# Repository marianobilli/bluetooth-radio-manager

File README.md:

# Bluetooth Radio Manager

A self-contained, battery-powered box that puts **four 2.4 GHz radios** under one **ESP32-S3**, with a small OLED and encoder UI, in a 3D-printed case. Each radio slot takes an nRF24L01+PA+LNA or an Ebyte E01-2G4M27D, and the firmware decides what the four radios do: range tests, multi-channel sniffing, relays, mesh experiments, or anything else that needs several 2.4 GHz radios in one hand-held unit.

Everything is open: the KiCad board, the parametric case, the fab files and the firmware skeleton are in this repository.

## Contents

1. [Overview](#1-overview)
2. [PCB and components](#2-pcb-and-components)
3. [Ordering the PCB](#3-ordering-the-pcb)
4. [Ordering the case](#4-ordering-the-case)
5. [Firmware skeleton](#5-firmware-skeleton)

---

## 1. Overview

| | |
|---|---|
| **Radios** | 4 slots, 2×4 socket each, nRF24L01+PA+LNA or E01-2G4M27D, SMA antennas out the back |
| **Controller** | YD-ESP32-23 (ESP32-S3 DevKitC-1 clone, 16 MB flash, 8 MB PSRAM), socketed |
| **UI** | 1.3" I²C OLED, EC11 encoder with push, BACK and CONFIRM buttons, on a plug-in module |
| **Power** | Two 5 V USB-C sockets in the case: one supply of 2 A or more, or two smaller power banks. 3.5 to 10 h of continuous transmit |
| **Board** | 96.5 × 73.2 mm, 2 layers, all through-hole and socketed, hand-solderable |
| **Case** | Two-part 3D print, snap latches, vented, 103 × 103 × 26 mm, 41 mm to the top of the knob, antennas extra. One case fits either radio |
| **Firmware** | PlatformIO, Arduino framework, native and on-device tests |

The carrier board does only three things: power the radios correctly, wire them to one SPI bus with separate select and interrupt lines, and hold the modules so they can be swapped without tools. Everything else is firmware.

---

## 2. PCB and components

### Bill of materials

| Ref | Part | Role |
|-----|------|------|
| M1–M4 | 2×4 female header, 2.54 mm | Radio slots, along the top edge so the modules and antennas hang off the board |
| U1 | YD-ESP32-23 on 2 × 1×22 female headers | Controller, drives all four radios over one SPI bus |
| J1 | UI module on 1×9 female header + 4 × M3 standoffs | OLED, encoder, BACK and CONFIRM buttons |
| U2 | LD1117V33, TO-220, mounted flat | Shared 3.3 V rail for nRF24 slots, 800 mA |
| D1 | 1N5819 Schottky, DO-41 | Feeds the devkit from input A and stops its USB power reaching the radios |
| D2, D3 | SB240 Schottky (40 V, 2 A), DO-15 | Cross-feed between inputs A and B, so one supply can power the whole board |
| JP1–JP4 | 1×3 pin header + shunt | Radio slot supply select, 5 V or 3.3 V |
| C3–C6 | 220 µF / 10 V electrolytic | Bulk capacitor per radio slot, for TX bursts |
| C7–C10 | 100 nF ceramic | Decoupling per radio slot |
| C1, C2 | 470 µF / 10 V electrolytic | Bulk capacitor on each 5 V input |
| C11, C12 | 10 µF / 16 V electrolytic | LD1117 input and output |
| J2, J3 | JST-XH 2-pin | 5 V inputs A and B, pigtails from the case's USB-C sockets |
| MH1–MH4 | M3 holes | Case mounting |

### Radio modules and jumpers

Both modules share the nRF24L01 2×4 pinout (GND, VCC, CE, CSN, SCK, MOSI, MISO, IRQ), so either fits any slot. Each slot has a jumper selecting its supply. Fit **one** shunt per slot, or none to leave the slot unpowered.

| | nRF24L01+PA+LNA | E01-2G4M27D |
|---|---|---|
| Max TX power | 20 dBm (100 mW) | 27 dBm (500 mW) |
| VCC | 1.9–3.6 V | 2.5–5.5 V |
| TX current | ~115 mA @ 3.3 V | 390 mA @ 5 V |
| **Jumper** | **3V3** (pins 2-3) | **5V** (pins 1-2) |

> **Warning:** a shunt on `5V` with an nRF24L01+PA+LNA fitted destroys the module. Check the jumpers before applying power. The silkscreen next to the jumpers repeats this.

Mechanically the two differ: the nRF24 is 41 × 15.5 mm with its SMA jack standing on the board, the E01 is 33.2 × 18 mm with a 3.7 mm shield can and an edge-mount SMA at the board end. Both are modelled, and the board exists in two files that differ only in which module the sockets show: `bt_radio_manager.kicad_pcb` with nRF24s (the one to order from) and `bt_radio_manager_e01.kicad_pcb` with E01s, for checking the fit and seeing the finished product with each radio.

### Pin map

| Function | GPIO | | Function | GPIO |
|----------|------|-|----------|------|
| SPI SCK / MOSI / MISO | IO12 / IO11 / IO2 | | I²C SDA / SCL | IO14 / IO13 |
| Radio 1 CE / CSN / IRQ | IO7 / IO1 / IO15 | | Encoder A / B / push | IO5 / IO4 / IO6 |
| Radio 2 CE / CSN / IRQ | IO9 / IO8 / IO16 | | CONFIRM button | IO21 |
| Radio 3 CE / CSN / IRQ | IO17 / IO10 / IO18 | | BACK button | IO38 |
| Radio 4 CE / CSN / IRQ | IO40 / IO39 / IO41 | | | |

### Power

Input A feeds the ESP32 (through D1) and radio slots 1–2; input B feeds slots 3–4 and the 3.3 V regulator. The devkit's own 3.3 V regulator supplies the UI module. D2 and D3 join the two rails in opposite directions, so the board runs from one supply or from two:

- **Two supplies, one per socket.** Each rail runs from its own input, and the diodes stay off while the two inputs are within about 0.3 V of each other. Each power-bank port then carries about 1 A at most.
- **One supply.** Plug it into input A, the socket wired to J2; the silkscreen says "1 SUPPLY: J2". Rail B is then fed through D2 and sits about 0.45 V lower, around 4.5 V, which the E01s and the LD1117 both accept. Input B alone also works, but the devkit then sees two diode drops, about 4.2 V on its 5 V pin.
- **Sizing a single supply.** It carries the whole load, about 1.9 A with four E01s transmitting. Use a 5 V 3 A USB-C adapter or a power-bank port rated 2.4 A or more.

D1 matters when programming without a power bank: the devkit passes its USB VBUS out through its 5 V pin, so without the diode a PC port would also be powering any E01 jumpered to 5 V on slots 1–2. With it the PC feeds only the devkit.

| All four radios transmitting | Draw at 5 V | 10,000 mAh power bank |
|---|---|---|
| 4 × E01-2G4M27D | ~1.7 A (8.6 W) | ~3.5–4 h |
| 4 × nRF24L01+PA+LNA | ~0.6 A (3.1 W) | ~10 h |

### Design notes

- **A jumper per slot instead of a regulator per slot.** The E01 runs straight from 5 V and keeps 3.3 V logic; only the nRF24 needs 3.3 V, and one LDO covers all four at nRF24 currents. This removed four buck modules from an earlier revision.
- **A linear regulator, not a buck.** PA/LNA radios amplify supply noise. The LD1117 has no switching ripple and dissipates at most 0.8 W, fine for a TO-220 without a heatsink.
- **Decoupling at every slot**, 220 µF + 100 nF next to each socket for 490 mA TX bursts, 470 µF on each input for cable and power-bank response.
- **Space under the modules.** The devkit and UI module sit 11 mm above the board. U2 lies flat under the OLED, and a mounting hole sits under the devkit's USB end where plug insertion pushes hardest.
- **Routing.** GND pour on both layers. Power nets 0.6 to 1.0 mm, with 1.0 mm from each input to the cross-feed diodes, which carry the whole load on a single supply. Signals 0.2 mm, 14 vias. The SPI bus is shared, each radio has its own CE, CSN and IRQ.

### Design files

| Path | Contents |
|------|----------|
| `hardware/kicad/bt_radio_manager.kicad_sch` / `.kicad_pcb` | KiCad 10 schematic and layout |
| `hardware/kicad/bt_radio_manager_e01.kicad_pcb` | The same layout with the E01-2G4M27D in the radio sockets, for 3D viewing and the case check |
| `hardware/kicad/bt_tester_parts.pretty/` | Custom footprints: radio socket (one each showing the nRF24 and the E01), YD-ESP32-23, UI module |
| `hardware/kicad/bt_tester_parts.3dshapes/` | STEP models (nRF24L01+PA+LNA, E01-2G4M27D, antenna, devkit, UI module) and the Python scripts that generate them |
| `docs/E01-2G4M27D_Usermanual_EN_v1.3.pdf` | E01 manual, source of its pinout and dimensions |

---

## 3. Ordering the PCB

Upload **`hardware/kicad/bt_radio_manager_gerbers.zip`**. It holds the nine Gerber layers, the PTH and NPTH Excellon drill files and the job file, as exported by KiCad 10. Any board house that takes Gerbers works.

| Parameter | Value |
|-----------|-------|
| Layers | 2 |
| Size | 96.5 × 73.2 mm |
| Material / thickness | FR-4, 1.6 mm |
| Copper | 1 oz (35 µm) outer |
| Surface finish | HASL lead-free is enough; ENIG if offered at no cost |
| Solder mask | any colour, both sides |
| Silkscreen | both sides, white. The back carries the logo and the version mark |
| Min track / clearance | 0.2 mm / 0.2 mm |
| Min hole | 0.3 mm (vias), plated. Largest 1.2 mm. Two NPTH sizes for the mounting holes |
| Via | 0.6 mm pad, 0.3 mm drill |
| Castellations, impedance control, stencil, assembly | none needed, everything is through-hole and hand-soldered |
| Quantity | 5 is the usual minimum |

The defaults on JLCPCB, PCBWay or Aisler all satisfy this. Order the parts in the bill of materials alongside; the modules, devkit and UI module parts come from the usual module sellers, the rest from any distributor.

---

## 4. Ordering the case

Upload the two files in **`case/print/`**. Both are 1:1 in millimetres. Order one of each.

| File | Part | Size (mm) |
|------|------|-----------|
| `enclosure_base.stl` or `.step` | Base: tray, board standoffs, USB-C openings labelled "5V POWER", latch pockets, floor vents | 103.3 × 103.4 × 19.7 |
| `enclosure_lid.stl` or `.step` | Lid: flat deck with OLED window, encoder hole, flush flexure buttons, engraved logo, latch tabs, SMA guides | 108.3 × 108.4 × 23.2 |

The lid snaps onto the base with four flexible tabs that hook into pockets in the side walls, so the material has to tolerate about 1 mm of flex each time it's opened. The lid's extra 5 mm of length is the SMA guide ribs on the back wall.

| Process and material | Verdict |
|---|---|
| **MJF or SLS nylon, PA12** | Best. Tough, isotropic, no supports. Usually the default "nylon" option |
| **FDM, PETG** | Good and cheapest. See the settings below |
| FDM, PLA | Works, but goes brittle with age; the tabs may crack after a year |
| SLA / resin | Avoid, the latches will snap |

**Parameters to request:** PA12 nylon (or PETG on FDM), any colour, standard tolerance (±0.2 mm or ±0.3 %), no smoothing. Walls are 2.4 mm, floor 2.0, deck 1.6, latch tabs 1.4, all above the usual 1 mm minimum. Density is not applicable to nylon; 20 to 30 % infill on FDM.

### Printing on FDM (PETG): tell the printer this

Both parts are designed to print **without supports** in one specific orientation. Pass these instructions on with the files, because the slicer defaults get two of them wrong.

| Setting | Base | Lid |
|---|---|---|
| **Orientation** | Floor down on the bed, as in the file | **Upside down**: the flat top on the bed, latch tabs and SMA guides pointing up |
| **Supports** | **Off** | **Off** |
| Layer / nozzle | 0.2 mm / 0.4 mm | 0.2 mm / 0.4 mm |
| Perimeters | 4 | 4, so the latch tabs are solid |
| Infill | 20 to 30 % | 20 to 30 % |
| **Seam** | Anywhere | On the **narrow 1.4 mm edges of the four latch tabs**, never on their flat faces, and not "random" |

- **Why no supports.** The lid's top is one flat plane, so it sits fully on the bed. Everything else is a short bridge: the USB-C socket holes, the antenna notches, the latch-pocket catches and the floor of the engraved logo (3 to 5 mm spans). Supports inside the latch pockets or the USB-C holes are hard to clean out and ruin the snap fit or the socket grip. Leave bridge detection on.
- **Why the seam matters.** The latch tabs bend about 1 mm every time the lid comes off. A seam on a flat face is a column of weak spots exactly where the bending stress is highest, and the tab cracks there. Use the slicer's seam painting to put it on the tab edges.

**Hardware to buy with it:** 4 × M3 heat-set inserts (3 mm long, 4.2 mm OD) and 4 × M3 × 6 screws for the board, and 2 × USB-C panel-mount power sockets with 2-wire pigtails (13 × 5.11 mm snap-in body, 15.7 × 9 mm oval flange) for the front wall.

**Fitting the encoder knob.** The knob clears the lid by only about 0.75 mm, and pressing the encoder moves it down about 0.5 mm. Push the knob about 1 mm less far onto its shaft than it would go, so it doesn't rub on the lid.

The case is generated by `case/enclosure.py` with [build123d](https://build123d.readthedocs.io/), reading part positions from the KiCad board, so it follows the layout. Running it rewrites `case/print/`, checks the case against every part on both board variants, and shows the assembly in the VS Code OCP CAD Viewer. Every dimension is a parameter at the top of the script.

The same case takes either radio in any slot. The back wall sits just in front of the E01's SMA flange, so the longer nRF24's jack stands about 1 mm further out; the wall notches and support blocks are 18 mm wide for the E01 and the blocks are pocketed for its edge-mount SMA legs, and the deck clears the E01's shield can. Outside the wall, a pair of ribs on the lid straddles the square section of each SMA jack, which is the same width on both modules, so a module cannot swing sideways in its notch. Because of these ribs, take the lid off straight up by releasing the latches on both sides, rather than tilting it open on one side.

<p align="center"><em>Left: nRF24L01+PA+LNA. Right: E01-2G4M27D. Same case, lid translucent to show the modules through the back wall and the guide ribs either side of each SMA jack.</em></p>

**Viewing and regenerating the case.** You need KiCad 10 (the script calls `kicad-cli` from its default install path, set at the top of the script), Python 3 with `build123d` and `ocp_vscode`, and the *OCP CAD Viewer* extension in VS Code.

```bash
pip install build123d ocp_vscode
```

Open the OCP CAD Viewer panel in VS Code (Ctrl+K V), then run from the repository root:

```bash
python case/enclosure.py          # board with four nRF24L01+PA+LNA
python case/enclosure.py e01      # board with four E01-2G4M27D
```

Each run exports the chosen board from KiCad to STEP, builds the case, prints the clearance check for both board variants and the part sizes, rewrites `case/print/` and `case/out/`, and sends the board, base, lid and USB sockets to the viewer. `case/out/assembly_<radio>.step` holds the complete product with that radio fitted, for any other CAD program. Without the viewer open the script still runs and only reports that it could not reach it. Set `LID_LIFT` in the script to show the lid raised above the base.

---

## 5. Firmware skeleton

PlatformIO project, Arduino framework, two environments: `yd_esp32_23` for the board and `native` for logic tests on the computer.

```
├── platformio.ini                  # board, partitions, ports, test settings
├── src/main.cpp                    # application entry point
├── test/test_basic/                # logic tests, run native and on device
├── test/test_rgb_led/              # hardware smoke test, device only
├── partitions/partitions_16MB_psram.csv
└── AGENTS.md                       # rules for AI coding agents working here
```

**Setup.** Install PlatformIO (VS Code extension or `pip install platformio`). Plug the devkit's **UART** USB-C connector, not the one marked USB: it is a CH343P bridge that stays on the bus through resets, which the test runner needs. Find the port and put it in `platformio.ini`:

```ini
upload_port = COM3        ; or /dev/cu.usbmodem…, /dev/ttyUSB0
test_port   = COM3
```

**Commands:**

```bash
pio run                      # build
pio run --target upload      # flash
pio device monitor           # serial at 115200
pio test -e native           # logic tests, no board
pio test -e yd_esp32_23      # tests on the board
```

**What's there and what comes next.** `main.cpp` is a placeholder that flashes the devkit's onboard RGB LED, and the tests show the pattern for native and on-device Unity tests (see `how_to_unit_test.md`). The radio application builds on the pin map in section 2:

- one `SPIClass` on IO12 / IO11 / IO2, shared by all four radios;
- four radio drivers, one per slot, each with its own CE, CSN and IRQ pin, for example the RF24 library with `RF24(ce, csn)` per slot;
- the UI on I²C (IO14 / IO13) with an SSD1306 or SH1106 driver, the encoder on IO5 / IO4 with push on IO6, buttons on IO21 and IO38;
- whatever the four radios should do, as a state machine driven from `loop()`.

The custom partition table is required: the default one lacks the `otadata` partition at `0xe000` and the `coredump` partition, and without them the board fails to boot after flashing. `AGENTS.md` records that and the other board constraints for anyone, human or agent, changing the firmware.

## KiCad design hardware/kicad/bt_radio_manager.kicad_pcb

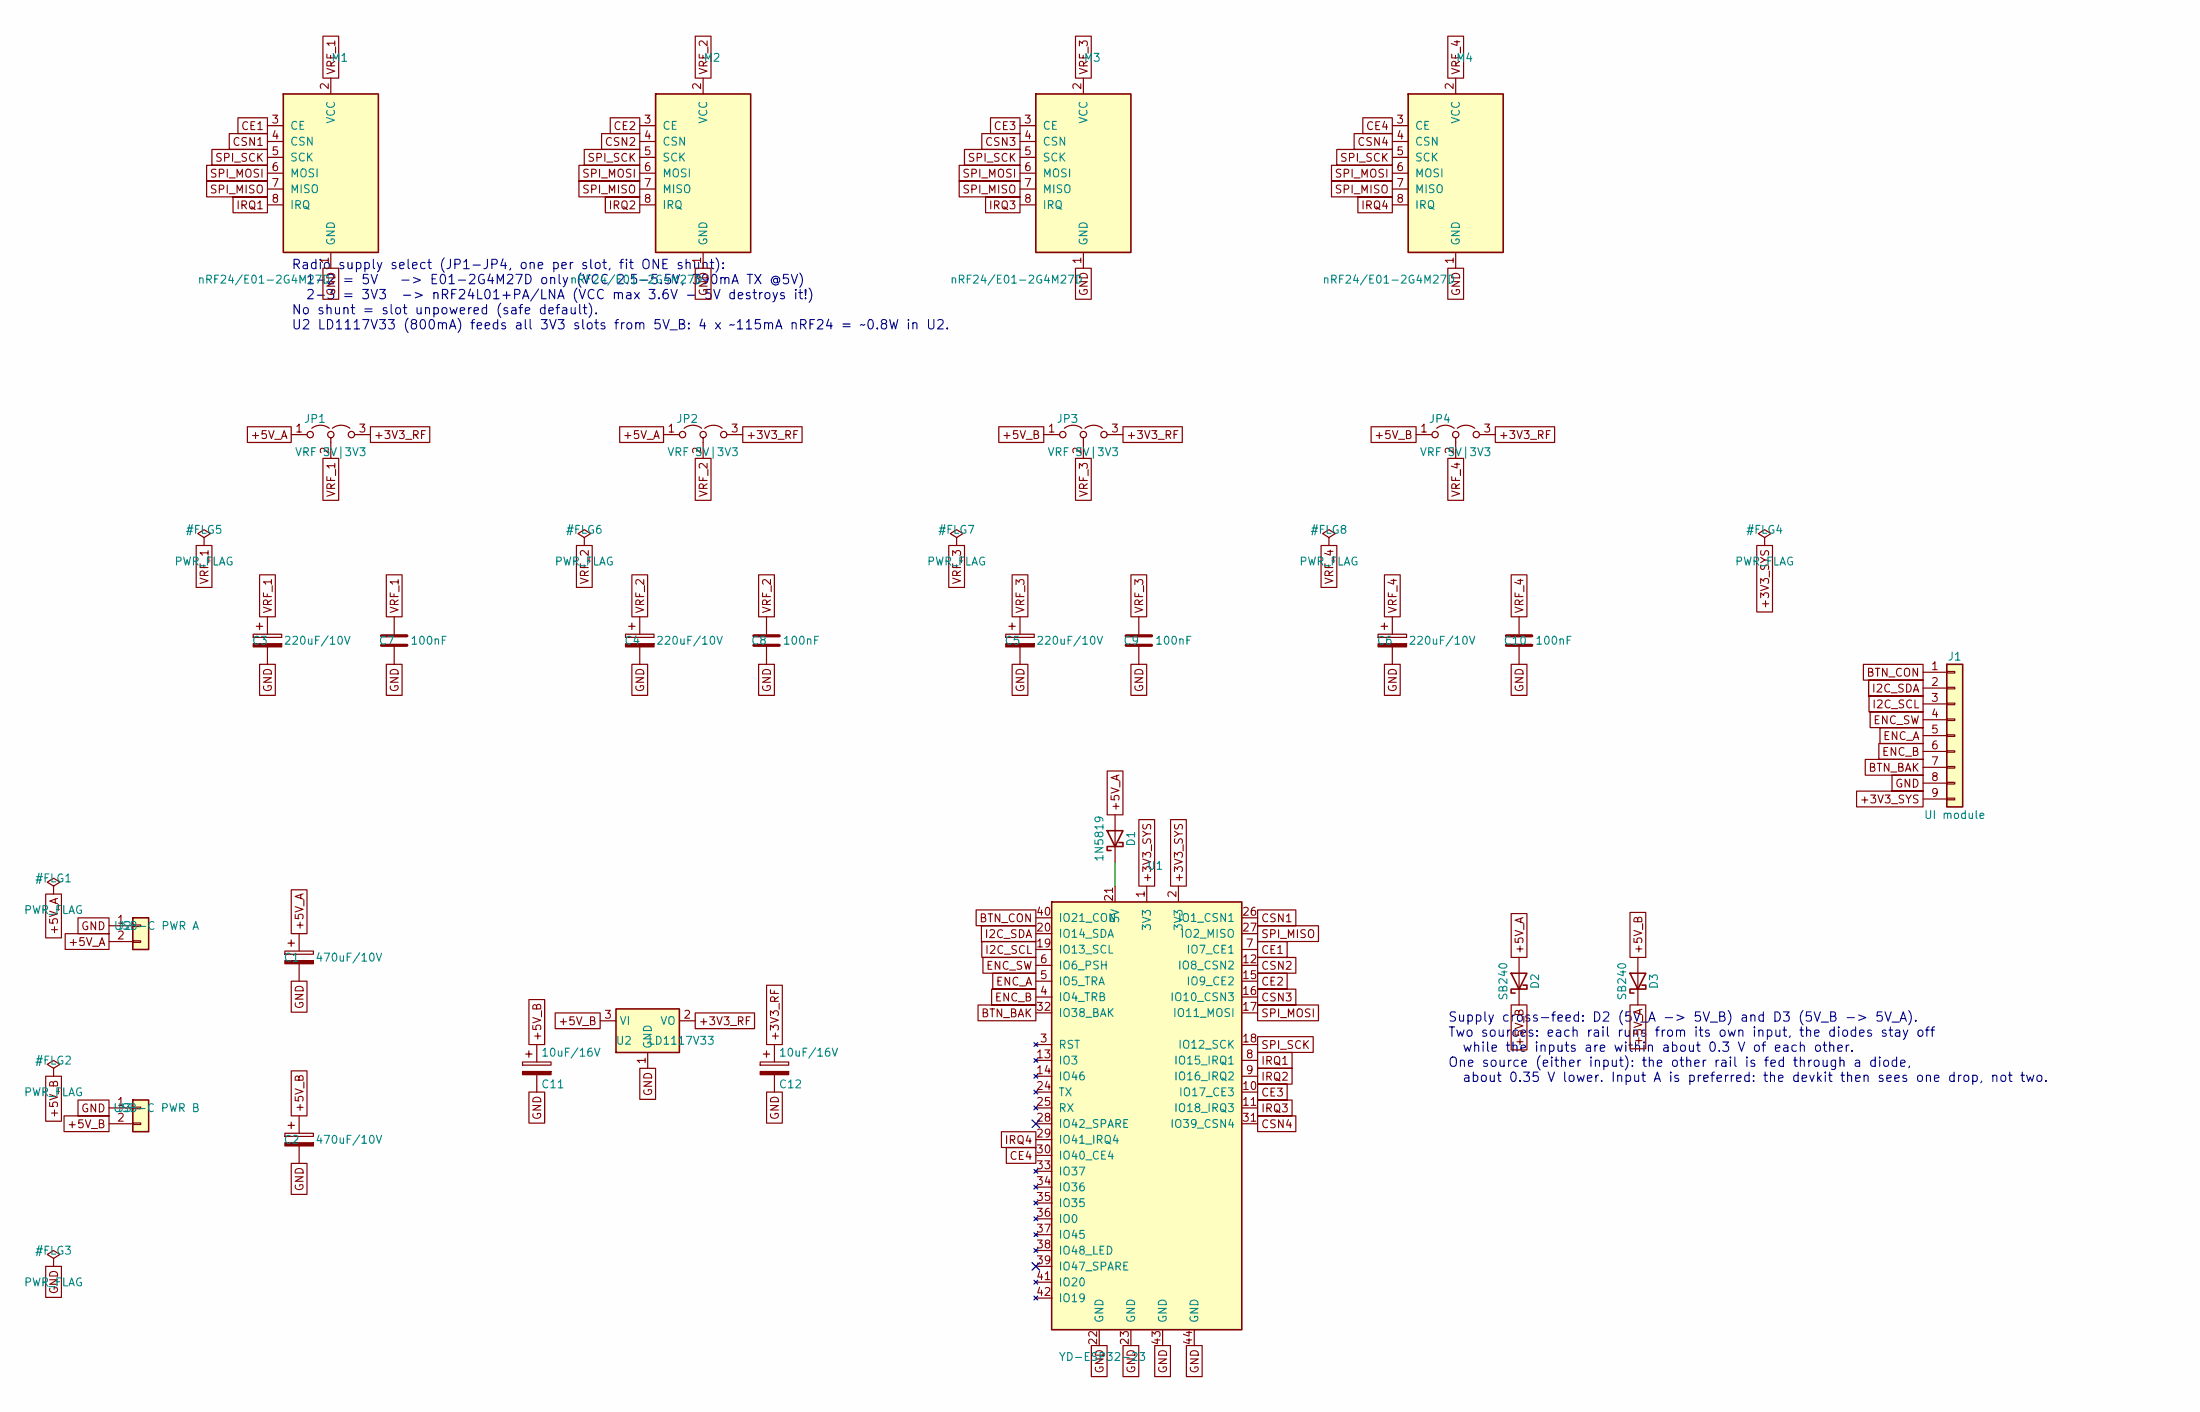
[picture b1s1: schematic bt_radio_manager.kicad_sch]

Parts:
C1, C2: 470uF/10V; CP_Radial_D8.0mm_P3.50mm
C3, C4, C5, C6: 220uF/10V; CP_Radial_D6.3mm_P2.50mm
C7, C8, C9, C10: 100nF; C_Disc_D5.0mm_W2.5mm_P5.00mm
C11, C12: 10uF/16V; CP_Radial_D5.0mm_P2.00mm
D1: 1N5819; D_DO-41_SOD81_P10.16mm_Horizontal
D2, D3: SB240; D_DO-15_P10.16mm_Horizontal
J1: UI module; UI_module_OLED_EC11
J2: USB-C PWR A; JST_XH_B2B-XH-A_1x02_P2.50mm_Vertical
J3: USB-C PWR B; JST_XH_B2B-XH-A_1x02_P2.50mm_Vertical
JP1, JP2, JP3, JP4: VRF 5V|3V3; PinHeader_1x03_P2.54mm_Vertical
M1, M2, M3, M4: nRF24/E01-2G4M27D; nRF24_module_2x4
U1: YD-ESP32-23
U2: LD1117V33; TO-220-3_Horizontal_TabDown

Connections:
+3V3_RF: C12.1, JP1.3 (B), JP2.3 (B), JP3.3 (B), JP4.3 (B), U2.2 (VO)
+3V3_SYS: J1.9, U1.1 (3V3), U1.2 (3V3)
+5V_A: C1.1, D1.2 (A), D2.2 (A), D3.1 (K), J2.2, JP1.1 (A), JP2.1 (A)
+5V_B: C2.1, C11.1, D2.1 (K), D3.2 (A), J3.2, JP3.1 (A), JP4.1 (A), U2.3 (VI)
BTN_BAK: J1.7, U1.32 (IO38_BAK)
BTN_CON: J1.1, U1.40 (IO21_CON)
CE1: M1.3 (CE), U1.7 (IO7_CE1)
CE2: M2.3 (CE), U1.15 (IO9_CE2)
CE3: M3.3 (CE), U1.10 (IO17_CE3)
CE4: M4.3 (CE), U1.30 (IO40_CE4)
CSN1: M1.4 (CSN), U1.26 (IO1_CSN1)
CSN2: M2.4 (CSN), U1.12 (IO8_CSN2)
CSN3: M3.4 (CSN), U1.16 (IO10_CSN3)
CSN4: M4.4 (CSN), U1.31 (IO39_CSN4)
ENC_A: J1.5, U1.5 (IO5_TRA)
ENC_B: J1.6, U1.4 (IO4_TRB)
ENC_SW: J1.4, U1.6 (IO6_PSH)
GND: C1.2, C2.2, C3.2, C4.2, C5.2, C6.2, C7.2, C8.2, C9.2, C10.2, C11.2, C12.2, J1.8, J2.1, J3.1, M1.1 (GND), M2.1 (GND), M3.1 (GND), M4.1 (GND), U1.22 (GND), U1.23 (GND), U1.43 (GND), U1.44 (GND), U2.1 (GND)
I2C_SCL: J1.3, U1.19 (IO13_SCL)
I2C_SDA: J1.2, U1.20 (IO14_SDA)
IRQ1: M1.8 (IRQ), U1.8 (IO15_IRQ1)
IRQ2: M2.8 (IRQ), U1.9 (IO16_IRQ2)
IRQ3: M3.8 (IRQ), U1.11 (IO18_IRQ3)
IRQ4: M4.8 (IRQ), U1.29 (IO41_IRQ4)
unnamed: D1.1 (K), U1.21 (5V)
SPI_MISO: M1.7 (MISO), M2.7 (MISO), M3.7 (MISO), M4.7 (MISO), U1.27 (IO2_MISO)
SPI_MOSI: M1.6 (MOSI), M2.6 (MOSI), M3.6 (MOSI), M4.6 (MOSI), U1.17 (IO11_MOSI)
SPI_SCK: M1.5 (SCK), M2.5 (SCK), M3.5 (SCK), M4.5 (SCK), U1.18 (IO12_SCK)
VRF_1: C3.1, C7.1, JP1.2 (C), M1.2 (VCC)
VRF_2: C4.1, C8.1, JP2.2 (C), M2.2 (VCC)
VRF_3: C5.1, C9.1, JP3.2 (C), M3.2 (VCC)
VRF_4: C6.1, C10.1, JP4.2 (C), M4.2 (VCC)

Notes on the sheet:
Radio supply select (JP1-JP4, one per slot, fit ONE shunt): 1-2 = 5V -> E01-2G4M27D only (VCC 2.5-5.5V, 390mA TX @5V) 2-3 = 3V3 -> nRF24L01+PA/LNA (VCC max 3.6V - 5V destroys it!) No shunt = slot unpowered (safe default). U2 LD1117V33 (800mA) feeds all 3V3 slots from 5V_B: 4 x ~115mA nRF24 = ~0.8W 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
Supply cross-feed: D2 (5V_A -> 5V_B) and D3 (5V_B -> 5V_A). Two sources: each rail runs from its own input, the diodes stay off while the inputs are within about 0.3 V of each other. One source (either input): the other rail is fed through a diode, about 0.35 V lower. Input A is preferred: the devk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

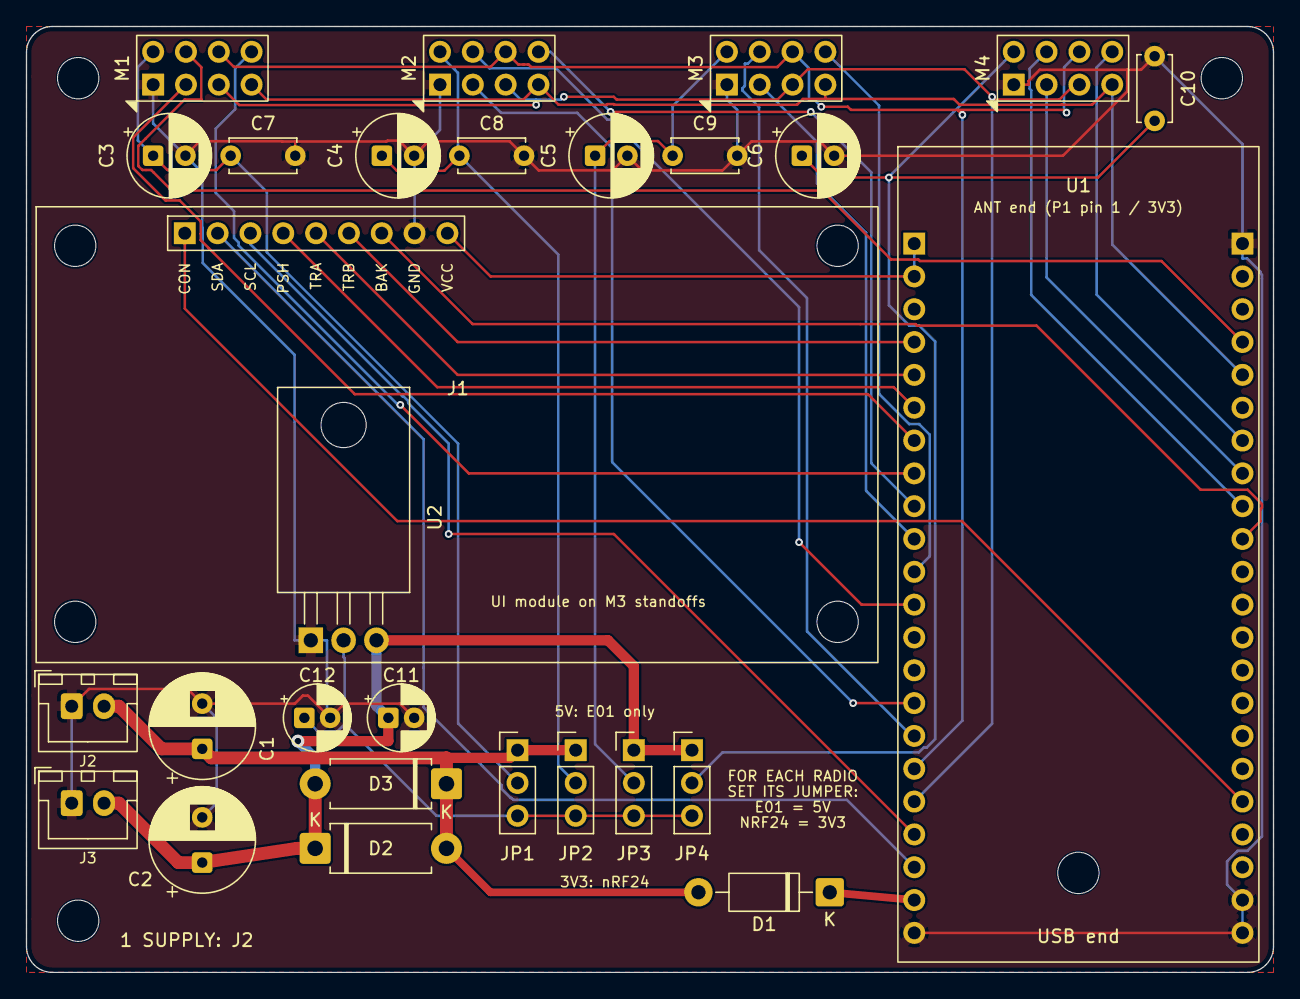
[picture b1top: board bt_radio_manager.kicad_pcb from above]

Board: 2 copper layers, 96.5 x 73.2 mm, 32 parts (0 on the bottom side), 32 nets.

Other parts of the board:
MH1, MH2, MH3, MH4: MountingHole_3.2mm; MountingHole_3.2mm_M3
